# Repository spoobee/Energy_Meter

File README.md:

# Energy_Meter
Mains Energy Meter

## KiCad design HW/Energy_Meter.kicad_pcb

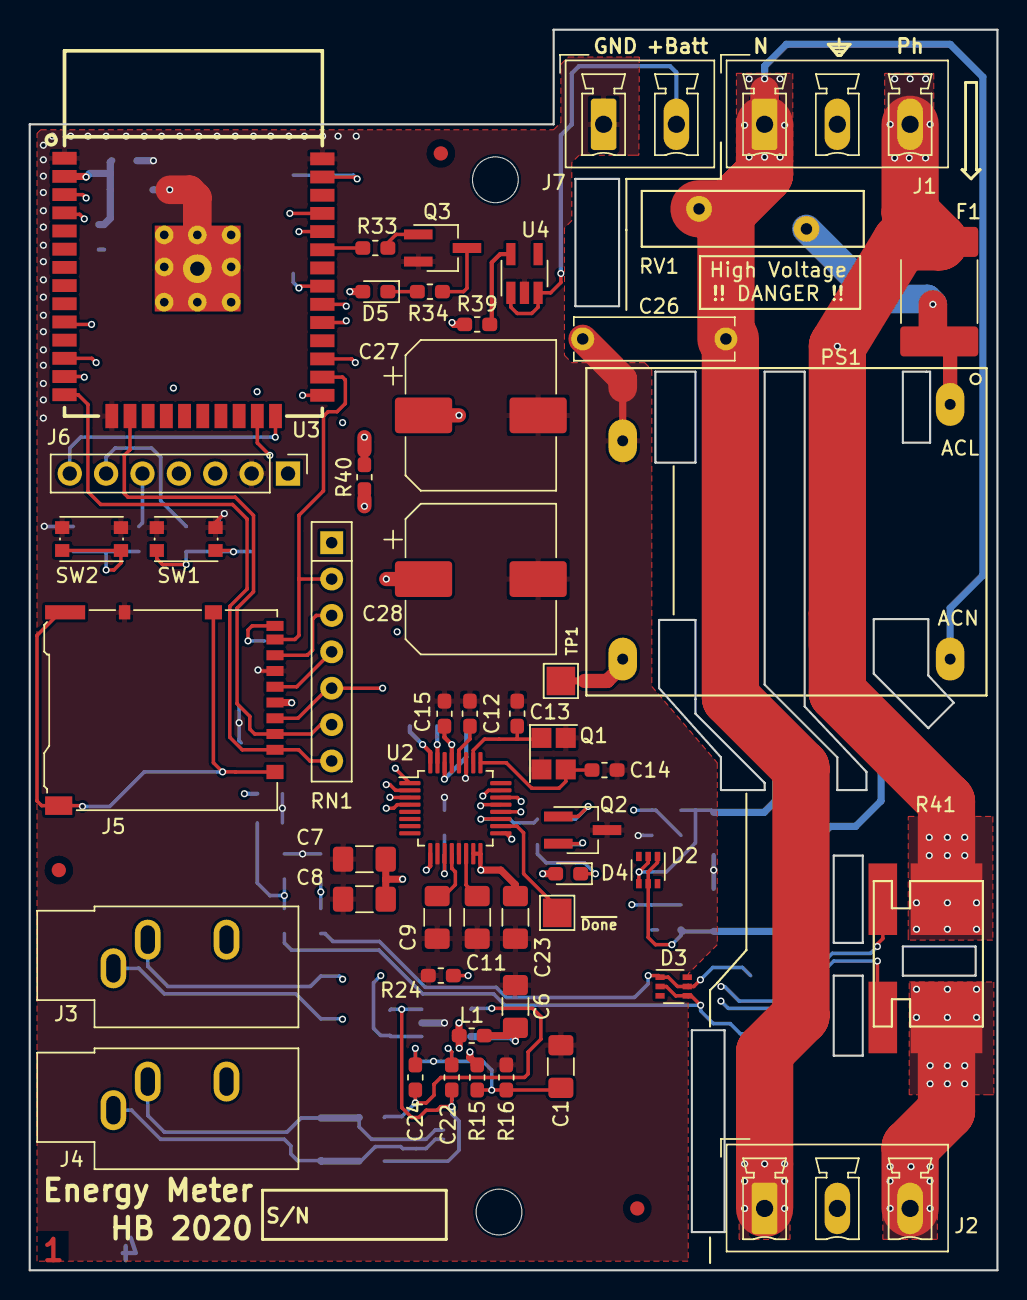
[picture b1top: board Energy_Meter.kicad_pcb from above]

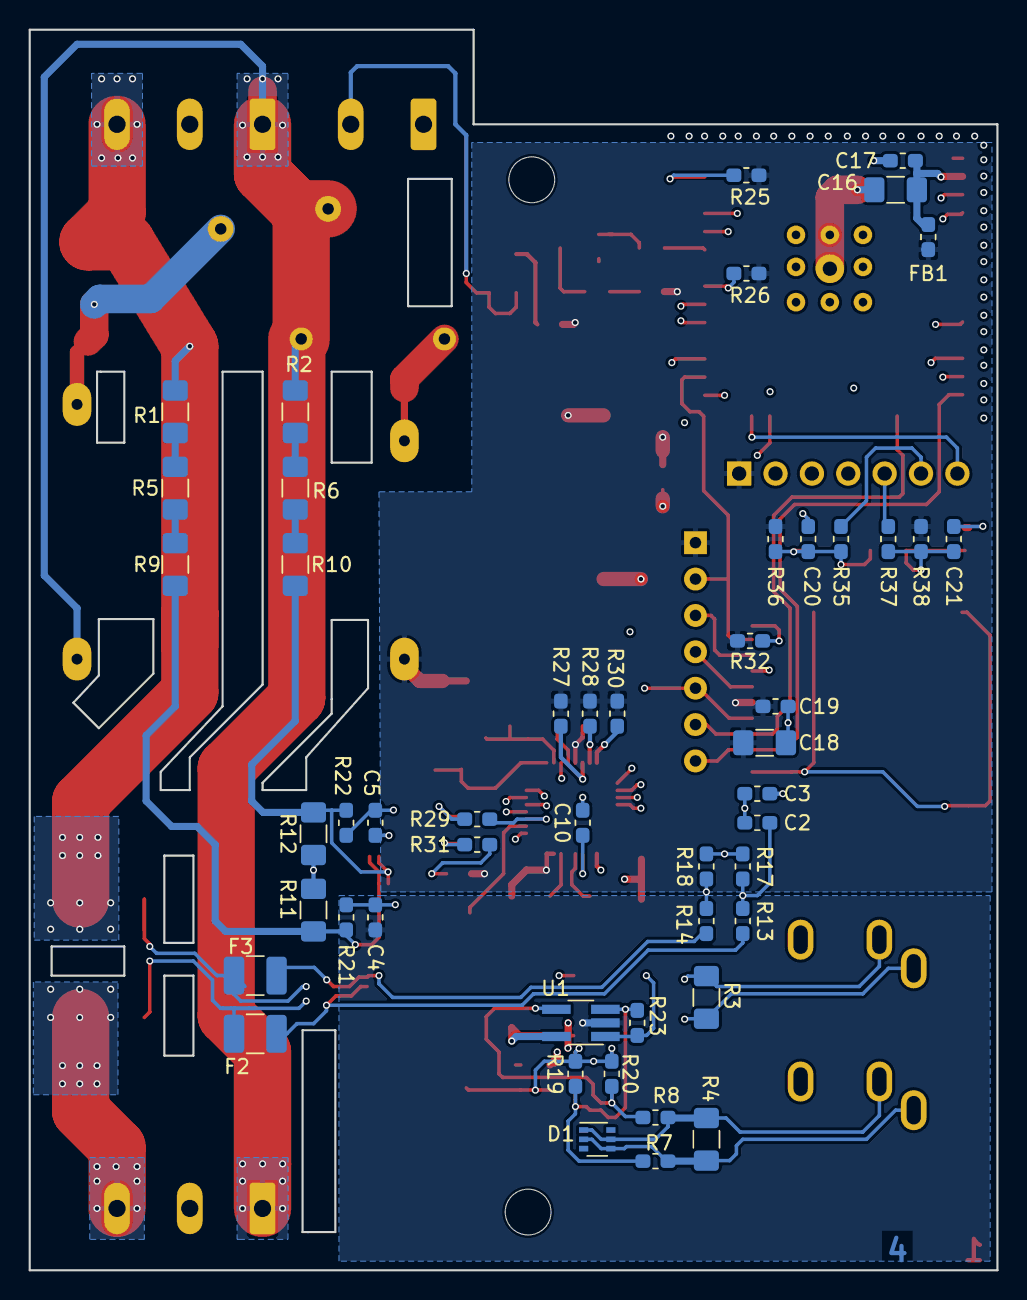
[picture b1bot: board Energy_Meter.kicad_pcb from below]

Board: 4 copper layers, 67.6 x 86.6 mm, 103 parts (49 on the bottom side), 67 nets.

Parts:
C1, C6, C7, C16, C18: 10uF; C_1206_3216Metric_Pad1.42x1.75mm_HandSolder
C2, C3, C22, C24: 1uF/16V; C_0603_1608Metric_Pad1.05x0.95mm_HandSolder
C4, C5: 470pF; C_0603_1608Metric_Pad1.05x0.95mm_HandSolder
C8, C9, C11, C23: 1uF; C_1206_3216Metric_Pad1.42x1.75mm_HandSolder
C10, C12: 270nF; C_0603_1608Metric_Pad1.05x0.95mm_HandSolder
C13, C14: C_Small; C_0603_1608Metric_Pad1.05x0.95mm_HandSolder
C15, C17, C19, C20, C21: 100nF; C_0603_1608Metric_Pad1.05x0.95mm_HandSolder
C26: 1nF/400V; C_Rect_L11.0mm_W2.8mm_P10.00mm_MKT
C27, C28: 470uF/25V; CP_Elec_10x10
D1, D2, D3: BAV99S; SOT-363_SC-70-6
D4: TOP_LEG_GREEN; LED_0603_1608Metric_Pad1.05x0.95mm_HandSolder
D5: LED_Small; LED_0603_1608Metric_Pad1.05x0.95mm_HandSolder
F1: Fuse_Small; Fuse_2920_7451Metric_Pad2.10x5.45mm_HandSolder
F2, F3: Fuse_Small; Fuse_1210_3225Metric_Pad1.42x2.65mm_HandSolder
FB1: Ferrite_Bead_Small; L_0603_1608Metric_Pad1.05x0.95mm_HandSolder
FID1, FID2, FID3: Fiducial; Fiducial_1mm_Mask2mm
H2, H3: MountingHole; MountingHole_3.2mm_M3_DIN965
J1, J2: Conn_01x03_Female; PhoenixContact_MCV_1,5_3-G-5.08_1x03_P5.08mm_Vertical
J3, J4: AudioJack3; Jack_3.5mm_CUI_SJ1-3533NG_Horizontal
J5: Micro_SD_Card_Det_Hirose_DM3AT; microSD_HC_Hirose_DM3AT-SF-PEJM5
J6: Conn_01x07_Female; PinHeader_1x07_P2.54mm_Vertical
J7: Conn_01x02_Female; PhoenixContact_MCV_1,5_2-G-5.08_1x02_P5.08mm_Vertical
L1: Ferrite_Bead_Small; L_0603_1608Metric_Pad1.05x0.95mm_HandSolder
PS1: RAC03-3.3SK; RAC03-XXSGB
Q1: ECS-163-18-5PXEN-TR; Crystal_SMD_3225-4Pin_3.2x2.5mm
Q2, Q3: Si2305CDS; SOT-23W_Handsoldering
R1, R2, R5, R6, R9, R10: 220K; R_1206_3216Metric_Pad1.42x1.75mm_HandSolder
R3, R4: 33; R_1206_3216Metric_Pad1.42x1.75mm_HandSolder
R7, R8, R13, R14, R17, R18, R19, R20, R21, R22: 10K/0.1%; R_0603_1608Metric_Pad1.05x0.95mm_HandSolder
R11, R12: 800/0.1%; R_1206_3216Metric_Pad1.42x1.75mm_HandSolder
R15, R16: 1K/0.1%; R_0603_1608Metric_Pad1.05x0.95mm_HandSolder
R23: 100K/0.1%; R_0603_1608Metric_Pad1.05x0.95mm_HandSolder
R24: 47K; R_0603_1608Metric_Pad1.05x0.95mm_HandSolder
R25, R26, R27, R28, R30: 750; R_0603_1608Metric_Pad1.05x0.95mm_HandSolder
R29, R33: 100K; R_0603_1608Metric_Pad1.05x0.95mm_HandSolder
R31: 47; R_0603_1608Metric_Pad1.05x0.95mm_HandSolder
R32: 4K7; R_0603_1608Metric_Pad1.05x0.95mm_HandSolder
R34, R35, R37: 220; R_0603_1608Metric_Pad1.05x0.95mm_HandSolder
R36, R38: 10K; R_0603_1608Metric_Pad1.05x0.95mm_HandSolder
R39, R40: 4.7; R_0603_1608Metric_Pad1.05x0.95mm_HandSolder
R41: CSS4J; CSS4J-4026R-1L00F
RN1: 4K7; R_Array_SIP7
RV1: Varistor; RV_Disc_D15.5mm_W3.9mm_P7.5mm
SW1, SW2: SW_Push; SW_Push_1P1T_NO_CK_KMR2
TP1: TestPoint_Alt; TestPoint_Pad_2.0x2.0mm
U1: AD8603; TSOT-23-5_HandSoldering
U2: ADS131A02; LQFP-32_5x5mm_P0.5mm
U3: ESP32-WROVER(_PCB,_IPEX,-xB)_and_ESP-WROOM-32-Uni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; ESP-WROOM-32_MODULE
U4: TLV75533PDBV; SOT-23-5_HandSoldering

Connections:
+3.3VA: C7.1, C8.1, C28.1, L1.1, R15.1, R40.1, U2.9
+3V3: C15.1, C18.1, C19.2, C23.1, C27.1, D4.2, D5.2, FB1.1, J5.4, J6.1, PS1.3, R25.2, R26.2, R27.2, R28.2, R30.2, R32.2, R36.1, R38.1, R39.1, R40.2, RN1.1, TP1.1, U2.15, U2.16, U2.29
/CPU_IoT/ALIVE: R33.1, U3.33
/CPU_IoT/DIN_MASTER_SPI: R26.1, U2.21, U3.31
/CPU_IoT/EN: J6.6, R35.2, U3.3
/CPU_IoT/GPIO0: J6.5, R37.2, U3.25
/CPU_IoT/RxD0: J6.4, U3.34
/CPU_IoT/SCLK_SPI: U2.22, U3.30
/CPU_IoT/SD_CLK: J5.5, RN1.4, U3.13
/CPU_IoT/SD_CMD: J5.3, RN1.5, U3.23
/CPU_IoT/SD_DATA0: J5.7, J6.7, RN1.3, U3.24
/CPU_IoT/SD_DATA1: J5.8, RN1.2, U3.26
/CPU_IoT/SD_DATA2: J5.1, RN1.7, U3.14
/CPU_IoT/SD_DATA3: J5.2, RN1.6, U3.16
/CPU_IoT/SD_DET: J5.9, R32.1, U3.27
/CPU_IoT/TxD0: J6.3, U3.35
/CPU_IoT/~CS_SPI: U2.23, U3.29
/CPU_IoT/~DRDY_SPI: R29.1, U2.19, U3.10
/CPU_IoT/~RESET: U2.17, U3.12
/Measurements/ADC_I_Homopolar: R23.1, R24.1, U1.1, U3.4
/Measurements/DIN_SPI: R25.1, U2.20, U3.37
/Measurements/I_HOMO_N: D1.1, D1.5, J4.T, R4.2, R8.2
/Measurements/I_HOMO_P: D1.2, D1.4, J4.S, R4.1, R7.2
/Measurements/I_MEAS_N: C3.1, R14.2, R18.2, U2.3
/Measurements/I_MEAS_P: C2.2, R13.2, R17.1, U2.4
/Measurements/I_N: F3.1, J3.T, R3.2, R41.2
/Measurements/I_P: F2.1, J3.S, R3.1, R41.3
/Measurements/Neutral: C26.2, J1.1, J2.1, PS1.4, R2.2, RV1.2
/Measurements/PH: F1.1, J1.3, R1.2, R41.1
/Measurements/U_MEAS_N: C5.2, R22.1, U2.1
/Measurements/U_MEAS_P: C4.1, R21.1, U2.2
/Measurements/Vaa: C6.1, L1.2, U1.5
/Power/PH: F1.2, PS1.1, RV1.1
Earth: J1.2, J2.2
GND: C1.2, C2.1, C3.2, C4.2, C5.1, C6.2, C7.2, C8.2, C9.2, C10.2, C11.2, C12.2, C13.2, C14.2, C15.2, C16.2, C17.1, C18.2, C19.1, C20.2, C21.2, C23.2, C26.1, C27.2, C28.2, J5.6, J5.10, J6.2, J7.1, PS1.2, Q1.2, Q1.4, Q2.3, Q3.2, R11.1, R12.2, R16.2, R17.2, R18.1, R24.2, SW1.1, SW2.1, U1.2, U2.10, U2.13, U2.27, U3.1, U3.15, U3.38, U3.39, U4.2
unnamed: C1.1, C22.2, C24.1, R15.2, R16.1, R19.2, R20.1
unnamed: C9.1, U2.12
unnamed: C10.1, U2.11
unnamed: C11.1, U2.14
unnamed: C12.1, U2.28
unnamed: C13.1, Q1.1, U2.26
unnamed: C14.1, Q1.3, U2.25
unnamed: C16.1, C17.2, FB1.2, U3.2
unnamed: C20.1, R35.1, R36.2, SW1.2
unnamed: C21.1, R37.1, R38.2, SW2.2
unnamed: C22.1, R7.1, R19.1, R23.2, U1.3
unnamed: C24.2, R8.1, R20.2, U1.4
unnamed: D2.1, D2.5, R9.1, R11.2, R21.2
unnamed: D2.2, D2.4, R10.1, R12.1, R22.2
unnamed: D3.1, D3.5, F3.2, R14.1
unnamed: D3.2, D3.4, F2.2, R13.1
unnamed: D4.1, R31.2
unnamed: D5.1, R34.2
unnamed: J2.3, R41.4
unnamed: J7.2, U4.1, U4.3
unnamed: Q2.1, R29.2
unnamed: Q2.2, R31.1
unnamed: Q3.1, R33.2
unnamed: Q3.3, R34.1
unnamed: R1.1, R5.2
unnamed: R2.1, R6.2
unnamed: R5.1, R9.2
unnamed: R6.1, R10.2
unnamed: R27.1, U2.30
unnamed: R28.1, U2.31
unnamed: R30.1, U2.32
unnamed: R39.2, U4.5

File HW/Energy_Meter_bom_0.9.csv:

Component,Description,Part,References,Value,Footprint,Quantity Per PCB,Datasheet,Mouser Ref,Price
1,"Unpolarized capacitor, small symbol",C_Small,C2 C3,220pF,C_0603_1608Metric_Pad1.05x0.95mm_HandSolder,2,~,,
2,"Unpolarized capacitor, small symbol",C_Small,C4 C5,470pF,C_0603_1608Metric_Pad1.05x0.95mm_HandSolder,2,~,,
3,"Unpolarized capacitor, small symbol",C_Small,C15 C17 C19 C20 C21,100nF,C_0603_1608Metric_Pad1.05x0.95mm_HandSolder,5,~,,
4,"Unpolarized capacitor, small symbol",C_Small,C10 C12,270nF,C_0603_1608Metric_Pad1.05x0.95mm_HandSolder,2,~,,
5,"Unpolarized capacitor, small symbol",C_Small,C8 C9 C11 C23,1uF,C_1206_3216Metric_Pad1.42x1.75mm_HandSolder,4,~,,
6,"Polarized capacitor, small symbol",CP_Small,C1 C16 C18,10uF,C_1206_3216Metric_Pad1.42x1.75mm_HandSolder,3,~,,
7,"Unpolarized capacitor, small symbol",C_Small,C6 C7,10uF,C_1206_3216Metric_Pad1.42x1.75mm_HandSolder,2,~,,
8,"Unpolarized capacitor, small symbol",C_Small,C26,1nF/400V,C_Rect_L11.0mm_W2.8mm_P10.00mm_MKT,1,~,,
9,"Polarized capacitor, small symbol",CP_Small,C27 C28,470uF/25V,CP_Elec_10x10,2,~,,
10,"Unpolarized capacitor, small symbol",C_Small,C13 C14,C_Small,C_0603_1608Metric_Pad1.05x0.95mm_HandSolder,2,~,,
11,"High-speed switching diodes, dual series, SOT-363",BAV99S,D1 D2 D3,BAV99S,SOT-363_SC-70-6,3,https://assets.nexperia.com/documents/data-sheet/BAV99_SER.pdf,,
12,"Light emitting diode, small symbol",LED_Small,D4 D5,LED_Small,LED_0603_1608Metric_Pad1.05x0.95mm_HandSolder,2,~,,
13,"Fuse, small symbol",Fuse_Small,F1,Fuse_Small,Fuse_2920_7451Metric_Pad2.10x5.45mm_HandSolder,1,https://www.mouser.fr/datasheet/2/358/typ_UMF_250-1275961.pdf,,
14,"Ferrite bead, small symbol",Ferrite_Bead_Small,FB1 L1,Ferrite_Bead_Small,L_0603_1608Metric_Pad1.05x0.95mm_HandSolder,2,~,,
15,"Audio Jack, 3 Poles (Stereo / TRS)",AudioJack3,J3 J4,AudioJack3,Jack_3.5mm_CUI_SJ1-3533NG_Horizontal,2,https://www.mouser.fr/datasheet/2/670/sj1_353xng-1778850.pdf,490-SJ1-3533NG,0.98
16,"Generic connector, single row, 01x02, script generated (kicad-library-utils/schlib/autogen/connector/)",Conn_01x02_Female,J7,Conn_01x02_Female,"PhoenixContact_MCV_1,5_2-G-5.08_1x02_P5.08mm_Vertical",1,~,,
17,"Generic connector, single row, 01x03, script generated (kicad-library-utils/schlib/autogen/connector/)",Conn_01x03_Female,J1 J2,Conn_01x03_Female,"PhoenixContact_MCV_1,5_3-G-5.08_1x03_P5.08mm_Vertical",2,~,,
18,"Generic connector, single row, 01x07, script generated (kicad-library-utils/schlib/autogen/connector/)",Conn_01x07_Female,J6,Conn_01x07_Female,PinHeader_1x07_P2.54mm_Vertical,1,~,,
19,Micro SD Card Socket with card detection pins,Micro_SD_Card_Det_Hirose_DM3AT,J5,Micro_SD_Card_Det_Hirose_DM3AT,microSD_HC_Hirose_DM3AT-SF-PEJM5,1,https://www.hirose.com/product/en/download_file/key_name/DM3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,,
20,3 Watt Single Output EMC Class B AC/DC power supply with regulated and short-circuit-proof isolated DC outputs and low standby power consumption.,RAC03-3.3SGB,PS1,RAC03-3.3SK,RAC03-XXSGB,1,https://www.mouser.fr/datasheet/2/468/RAC03-K-1711241.pdf,919-RAC03-3.3SK,5.09
21,"Four pin crystal, GND on pins 2 and 4",Crystal_GND24,Q1,ECS-163-18-5PXEN-TR,,1,~,,
22,"-4.4A Id, -40V Vds, P-Channel MOSFET, SOT-23",Si2319CDS,Q2 Q3,Si2305CDS,SOT-23W_Handsoldering,2,https://www.vishay.com/docs/70833/70833.pdf,,
23,"P-MOSFET transistor, gate/source/drain",Q_PMOS_GSD,Q4,Si2315,SOT-23W_Handsoldering,1,~,,
24,"Resistor, small symbol",R_Small,R40,4.7,R_1206_3216Metric_Pad1.42x1.75mm_HandSolder,1,~,,
25,Resistor,R,R3 R4,33,R_1206_3216Metric_Pad1.42x1.75mm_HandSolder,2,~,,
26,"Resistor, small symbol",R_Small,R31 R34 R35 R37,220,R_0603_1608Metric_Pad1.05x0.95mm_HandSolder,4,~,,
27,"Resistor, small symbol",R_Small,R25 R26 R27 R28 R30,750,R_0603_1608Metric_Pad1.05x0.95mm_HandSolder,5,~,,
28,"Resistor, small symbol",R_Small,R32,4K7,R_0603_1608Metric_Pad1.05x0.95mm_HandSolder,1,~,,
29,"Resistor, small symbol",R_Small,R36 R38,10K,R_0603_1608Metric_Pad1.05x0.95mm_HandSolder,2,~,,
30,"Resistor, small symbol",R_Small,R24,47K,R_0603_1608Metric_Pad1.05x0.95mm_HandSolder,1,~,,
31,"Resistor, small symbol",R_Small,R29 R33,100K,R_0603_1608Metric_Pad1.05x0.95mm_HandSolder,2,~,,
32,"Resistor, small symbol",R_Small,R1 R2 R5 R6 R9 R10,220K,R_1206_3216Metric_Pad1.42x1.75mm_HandSolder,6,~,,
33,"Resistor, small symbol",R_Small,R13 R14 R21 R22,10K/0.1%,R_0603_1608Metric_Pad1.05x0.95mm_HandSolder,4,~,,
34,"Resistor, small symbol",R_Small,R15 R16,1K/0.1%,R_0603_1608Metric_Pad1.05x0.95mm_HandSolder,2,~,,
35,"Resistor, small symbol",R_Small,R17 R18,3K3/0.1%,R_0603_1608Metric_Pad1.05x0.95mm_HandSolder,2,~,,
36,Resistor,R,R7 R8,500/0.1%,R_0603_1608Metric_Pad1.05x0.95mm_HandSolder,2,~,,
37,"Resistor, small symbol",R_Small,R23,50K/0.1%,R_0603_1608Metric_Pad1.05x0.95mm_HandSolder,1,~,,
38,"Resistor, small symbol",R_Small,R19 R20,5K/0.1%,R_0603_1608Metric_Pad1.05x0.95mm_HandSolder,2,~,,
39,"Resistor, small symbol",R_Small,R11 R12,800/0.1%,R_1206_3216Metric_Pad1.42x1.75mm_HandSolder,2,~,,
40,Shunt resistor,R_Shunt,R41,CSS4J,CSS4J-4026R-1L00F,1,https://www.mouser.fr/datasheet/2/54/css4j-4026-1862184.pdf,652-CSS4J4026K5L00F,1.49
41,"6 resistor network, star topology, bussed resistors, small symbol",R_Network06,RN1,4K7,R_Array_SIP7,1,http://www.vishay.com/docs/31509/csc.pdf,,
42,Voltage dependent resistor,Varistor,RV1,Varistor,RV_Disc_D15.5mm_W3.9mm_P7.5mm,1,~,,
43,"Push button switch, generic, two pins",SW_Push,SW1 SW2,SW_Push,SW_Push_1P1T_NO_CK_KMR2,2,~,,
44,"Precision Micropower, Low Noise CMOS, Rail-to-Rail Input/Output Operational Amplifier, TSOT-23-5",AD8603,U1,AD8603,TSOT-23-5_HandSoldering,1,http://www.analog.com/media/en/technical-documentation/data-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,,
45,"ADS131A0x2- or 4-Channel,24-Bit,128-kSPS,Simultaneous-Sampling,Delta-SigmaADC",ADS131A02,U2,ADS131A02,LQFP-32_5x5mm_P0.5mm,1,http://www.ti.com/lit/ds/symlink/ads131a02.pdf,,
46,,"ESP32-WROVER(_PCB,_IPEX,-xB)_and_ESP-WROOM-32-Universal-OLIMEX_Cases",U3,"ESP32-WROVER(_PCB,_IPEX,-xB)_and_ESP-WROOM-32-Universal-OLIMEX_Cases",ESP-WROOM-32_MODULE,1,,,





Component Groups:,46
Component Count:,92
Fitted Components:,92
Number of PCBs:,1
Total components:,92
Schematic Version:,0.9
Schematic Date:,2020-04-17
PCB Variant:,['default']
BoM Date:,lun. 02 nov. 2020 00:08:37 CET
Schematic Source:,Energy_Meter.sch
KiCad Version:,Eeschema 5.1.7-a382d34a8~87~ubuntu18.04.1

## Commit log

2020-12-23 Create HW
